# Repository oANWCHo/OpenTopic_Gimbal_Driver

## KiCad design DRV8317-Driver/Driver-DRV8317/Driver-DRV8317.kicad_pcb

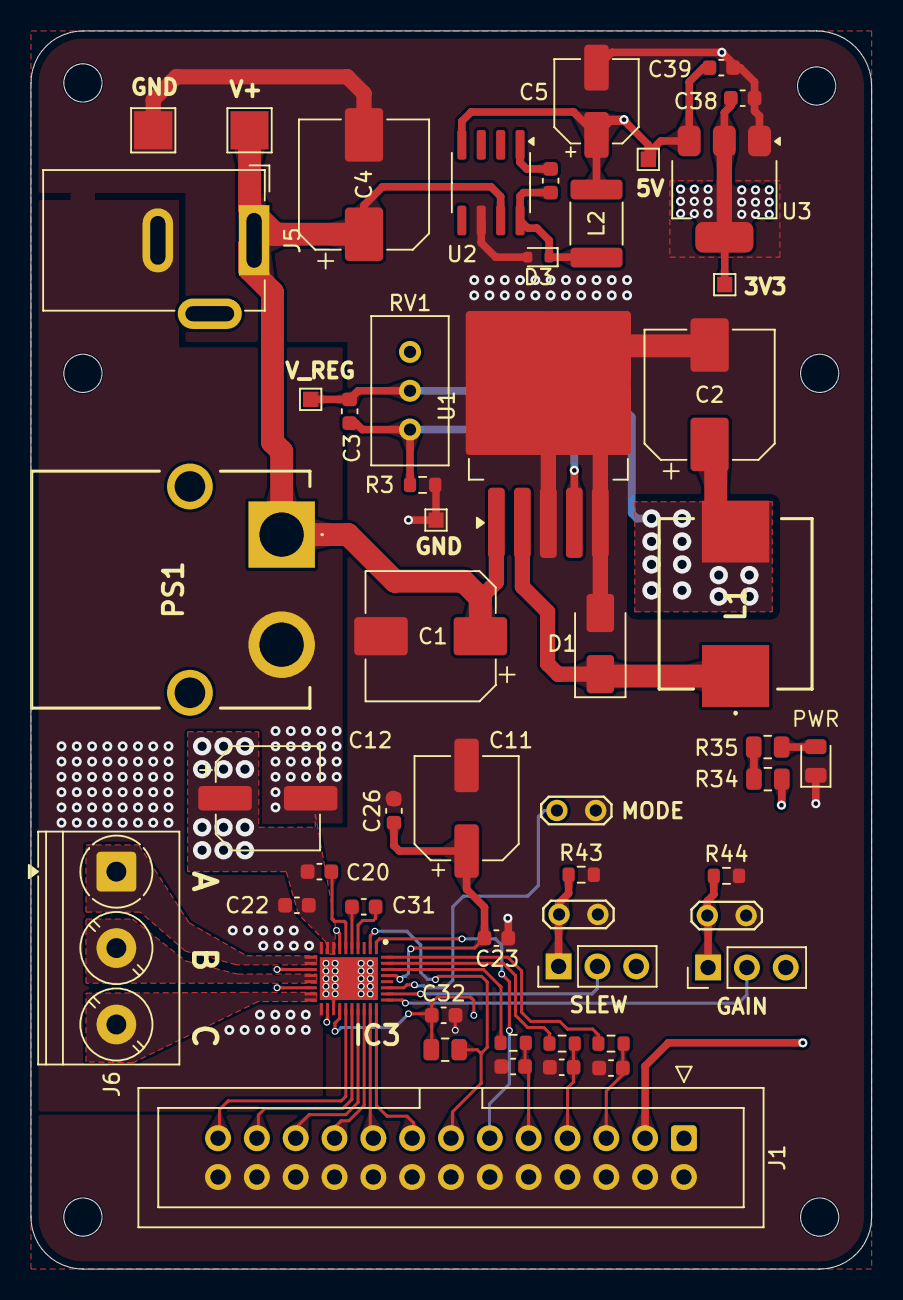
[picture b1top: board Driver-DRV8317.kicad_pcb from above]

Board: 4 copper layers, 55.0 x 81.0 mm, 59 parts (0 on the bottom side), 36 nets.

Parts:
C1: 330uF 35V; CP_Elec_8x10
C2, C4: 330uF 25V; CP_Elec_8x10
C3: 1.5nF; C_0603_1608Metric
C5: 100uF 10V; CP_Elec_5x5.3
C11, C12: 22uF 25V; CP_Elec_6.3x5.4
C20, C22, C23, C26, C31, C39: 0.1uF; C_0603_1608Metric
C28: 10nF; C_0603_1608Metric
C32: 2.2uF; C_0603_1608Metric
C33, C34, C35: 22pF; C_0603_1608Metric
C38: 10uF; C_0603_1608Metric
D1: 60V 3A; D_SMA
D3: 20V 500mA; D_SOD-523
D5: Red LED; LED_0805_2012Metric
H1, H2, H3, H4, H5, H6: MountingHole; MountingHole_2.5mm
IC3: DRV8317HREER; QFN40P400X500X80-37N-D
J1: Conn_02x13_Odd_Even; IDC-Header_2x13_P2.54mm_Vertical
J5: Jack-DC; BarrelJack_GCT_DCJ200-10-A_Horizontal
J6: Screw_Terminal_01x03; TerminalBlock_Phoenix_PT-1,5-3-5.0-H_1x03_P5.00mm_Horizontal
JP1: 0.25V/A; TestPoint_2Pads_Pitch2.54mm_Drill0.8mm
JP2: Gain Selector; PinHeader_1x03_P2.54mm_Vertical
JP3: Mode Selector; TestPoint_2Pads_Pitch2.54mm_Drill0.8mm
JP4: Slew Selector; PinHeader_1x03_P2.54mm_Vertical
JP5: 25V/us; TestPoint_2Pads_Pitch2.54mm_Drill0.8mm
L1: 47uH 3.1A; LMLP1011M470DTAS
L2: 47uH 3.1A; L_1812_4532Metric_Pad1.30x3.40mm_HandSolder
PS1: XT60PW-M; XT60PWM
R3: 1K; R_0603_1608Metric
R4, R5, R6: 330; R_0603_1608Metric
R34, R35: 3.6; R_0805_2012Metric
R42: 5k; R_0805_2012Metric
R43, R44: 47K; R_0603_1608Metric
RV1: R_Potentiometer_Trim; Potentiometer_Bourns_3296W_Vertical
TP1, TP2, TP3, TP7: TestPoint; TestPoint_Pad_1.0x1.0mm
TP8: V+; TestPoint_Pad_2.5x2.5mm
TP9: V-; TestPoint_Pad_2.5x2.5mm
U1: LM2596S-ADJ; TO-263-5_TabPin3
U2: LM2674M-5.0; SOIC-8_3.9x4.9mm_P1.27mm
U3: LD1117S33TR; SOT-223-3_TabPin2

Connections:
+5V: C5.1, C39.2, J1.3, L2.2, TP3.1, U2.4 (FB), U3.3 (VI)
/DRV8317/NFAULT: IC3.2 (NFAULT), J1.13, R42.1
/DRV8317/NSLEEP: IC3.1 (NSLEEP), J1.11
/DRV8317/TIM1_CH1: IC3.23 (INHA), J1.25
/DRV8317/TIM1_CH1N: IC3.24 (INLA), J1.23
/DRV8317/TIM1_CH2: IC3.25 (INHB), J1.21
/DRV8317/TIM1_CH2N: IC3.26 (INLB), J1.19
/DRV8317/TIM1_CH3: IC3.27 (INHC), J1.17
/DRV8317/TIM1_CH3N: IC3.28 (INLC), J1.15
/DRV8317/Vcurrfdbk_A: IC3.36 (SOA), R4.1
/DRV8317/Vcurrfdbk_B: IC3.35 (SOB), R5.1
/DRV8317/Vcurrfdbk_C: IC3.34 (SOC), R6.1
AVDD: C11.1, C23.1, C26.1, C32.1, C38.2, IC3.7 (VIN_AVDD), IC3.22 (AVDD), IC3.33 (CSAREF), J1.1, JP2.3 (B), JP4.3 (B), R34.1, R42.2, TP7.1, U3.2 (VO)
CP: C20.2, IC3.6 (CP)
CPH: C31.2, IC3.5 (CPH)
CPL: C31.1, IC3.4 (CPL)
GAIN: IC3.29 (GAIN), JP2.2 (C)
GND: C1.2, C2.2, C4.2, C5.2, C11.2, C12.2, C22.2, C23.2, C26.2, C32.2, C33.1, C34.1, C35.1, C38.1, C39.1, D1.2 (A), D3.2 (A), D5.1 (K), IC3.10 (PGND_1), IC3.13 (PGND_2), IC3.16 (PGND_3), IC3.19 (PGND_4), IC3.21 (AGND), IC3.37 (GND), J1.2, J1.4, J1.6, J1.8, J1.10, J1.12, J1.14, J1.16, J1.18, J1.20, J1.22, J1.24, J1.26, J5.2, JP1.2 (B), JP3.2 (B), JP5.2 (B), PS1.2 (-), R3.1, R43.2, R44.2, TP2.1, TP9.1, U1.3 (GND), U1.5 (~ON/OFF), U2.6 (GND), U3.1 (GND)
MODE: IC3.31 (MODE), JP3.1 (A)
unnamed: D1.1 (K), L1.1, U1.2 (OUT)
unnamed: C28.2, D3.1 (K), L2.1, U2.8 (VSW)
unnamed: D5.2 (A), R35.2
unnamed: IC3.11 (OUTA_1), IC3.12 (OUTA_2), J6.1
unnamed: IC3.14 (OUTB_1), IC3.15 (OUTB_2), J6.2
unnamed: IC3.17 (OUTC_1), IC3.18 (OUTC_2), J6.3
unnamed: C33.2, J1.5, R4.2
unnamed: C34.2, J1.7, R5.2
unnamed: C35.2, J1.9, R6.2
unnamed: JP1.1 (A), JP2.1 (A), R44.1
unnamed: JP4.1 (A), JP5.1 (A), R43.1
unnamed: R34.2, R35.1
unnamed: C3.1, R3.2, RV1.1, U1.4 (FB)
unnamed: C28.1, U2.1 (CB)
SLEW: IC3.30 (SLEW), JP4.2 (C)
V+: C1.1, C4.1, J5.1, PS1.1 (+), TP8.1, U1.1 (VIN), U2.7 (VIN)
VM: C2.1, C3.2, C12.1, C20.1, C22.1, IC3.8 (VM_1), IC3.9 (VM_2), IC3.20 (VM_3), L1.2, RV1.2, TP1.1

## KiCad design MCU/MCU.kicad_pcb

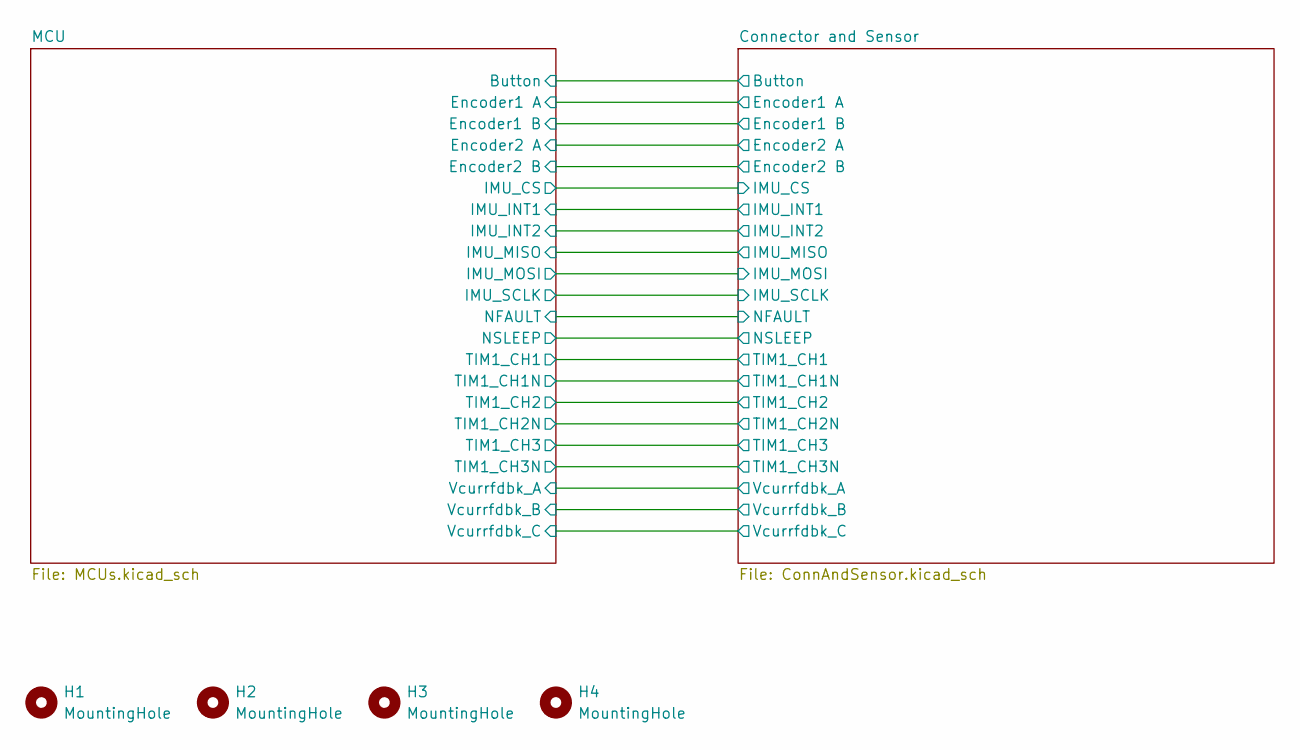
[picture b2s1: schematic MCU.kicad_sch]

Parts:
H1, H2, H3, H4: MountingHole; MountingHole_2.5mm

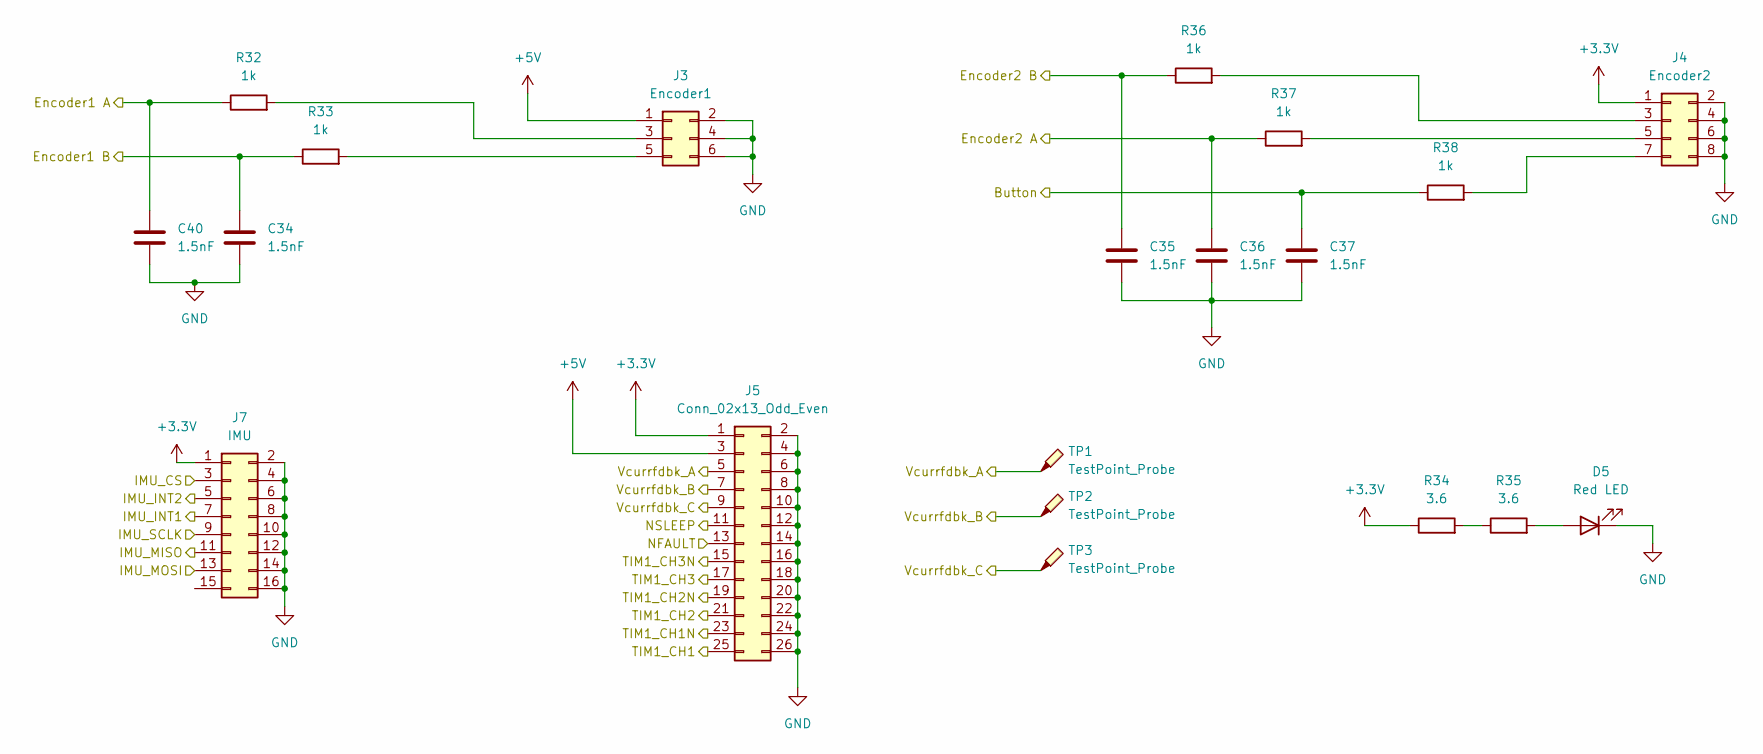
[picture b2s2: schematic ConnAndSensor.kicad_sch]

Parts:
C34, C35, C36, C37, C40: 1.5nF; C_0603_1608Metric
D5: Red LED; LED_0805_2012Metric
J3: Encoder1; IDC-Header_2x03_P2.54mm_Vertical
J4: Encoder2; IDC-Header_2x04_P2.54mm_Vertical
J5: Conn_02x13_Odd_Even; IDC-Header_2x13_P2.54mm_Vertical
J7: IMU; IDC-Header_2x08_P2.54mm_Vertical
R32, R33, R36, R37, R38: 1k; R_0603_1608Metric
R34, R35: 3.6; R_0805_2012Metric
TP1, TP2, TP3: TestPoint_Probe; TestPoint_Loop_D1.80mm_Drill1.0mm_Beaded

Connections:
+5V: J3.1, J5.3
/Connector and Sensor/Button: C37.2, R38.1; also elsewhere on the board
/Connector and Sensor/Encoder1 A: C40.2, R32.1; also elsewhere on the board
/Connector and Sensor/Encoder1 B: C34.2, R33.1; also elsewhere on the board
/Connector and Sensor/Encoder2 A: C36.2, R37.1; also elsewhere on the board
/Connector and Sensor/Encoder2 B: C35.2, R36.1; also elsewhere on the board
/Connector and Sensor/IMU_CS: J7.3; also elsewhere on the board
/Connector and Sensor/IMU_INT1: J7.7; also elsewhere on the board
/Connector and Sensor/IMU_INT2: J7.5; also elsewhere on the board
/Connector and Sensor/IMU_MISO: J7.11; also elsewhere on the board
/Connector and Sensor/IMU_MOSI: J7.13; also elsewhere on the board
/Connector and Sensor/IMU_SCLK: J7.9; also elsewhere on the board
/Connector and Sensor/NFAULT: J5.13; also elsewhere on the board
/Connector and Sensor/NSLEEP: J5.11; also elsewhere on the board
/Connector and Sensor/TIM1_CH1: J5.25; also elsewhere on the board
/Connector and Sensor/TIM1_CH1N: J5.23; also elsewhere on the board
/Connector and Sensor/TIM1_CH2: J5.21; also elsewhere on the board
/Connector and Sensor/TIM1_CH2N: J5.19; also elsewhere on the board
/Connector and Sensor/TIM1_CH3: J5.17; also elsewhere on the board
/Connector and Sensor/TIM1_CH3N: J5.15; also elsewhere on the board
/Connector and Sensor/Vcurrfdbk_A: J5.5, TP1.1; also elsewhere on the board
/Connector and Sensor/Vcurrfdbk_B: J5.7, TP2.1; also elsewhere on the board
/Connector and Sensor/Vcurrfdbk_C: J5.9, TP3.1; also elsewhere on the board
GND: C34.1, C35.1, C36.1, C37.1, C40.1, D5.1 (K), J3.2, J3.4, J3.6, J4.2, J4.4, J4.6, J4.8, J5.2, J5.4, J5.6, J5.8, J5.10, J5.12, J5.14, J5.16, J5.18, J5.20, J5.22, J5.24, J5.26, J7.2, J7.4, J7.6, J7.8, J7.10, J7.12, J7.14, J7.16; also elsewhere on the board
unnamed: D5.2 (A), R35.2
unnamed: J3.3, R32.2
unnamed: J3.5, R33.2
unnamed: J4.3, R36.2
unnamed: J4.5, R37.2
unnamed: J4.7, R38.2
unnamed: R34.2, R35.1
VDD: J4.1, J5.1, J7.1, R34.1; also elsewhere on the board

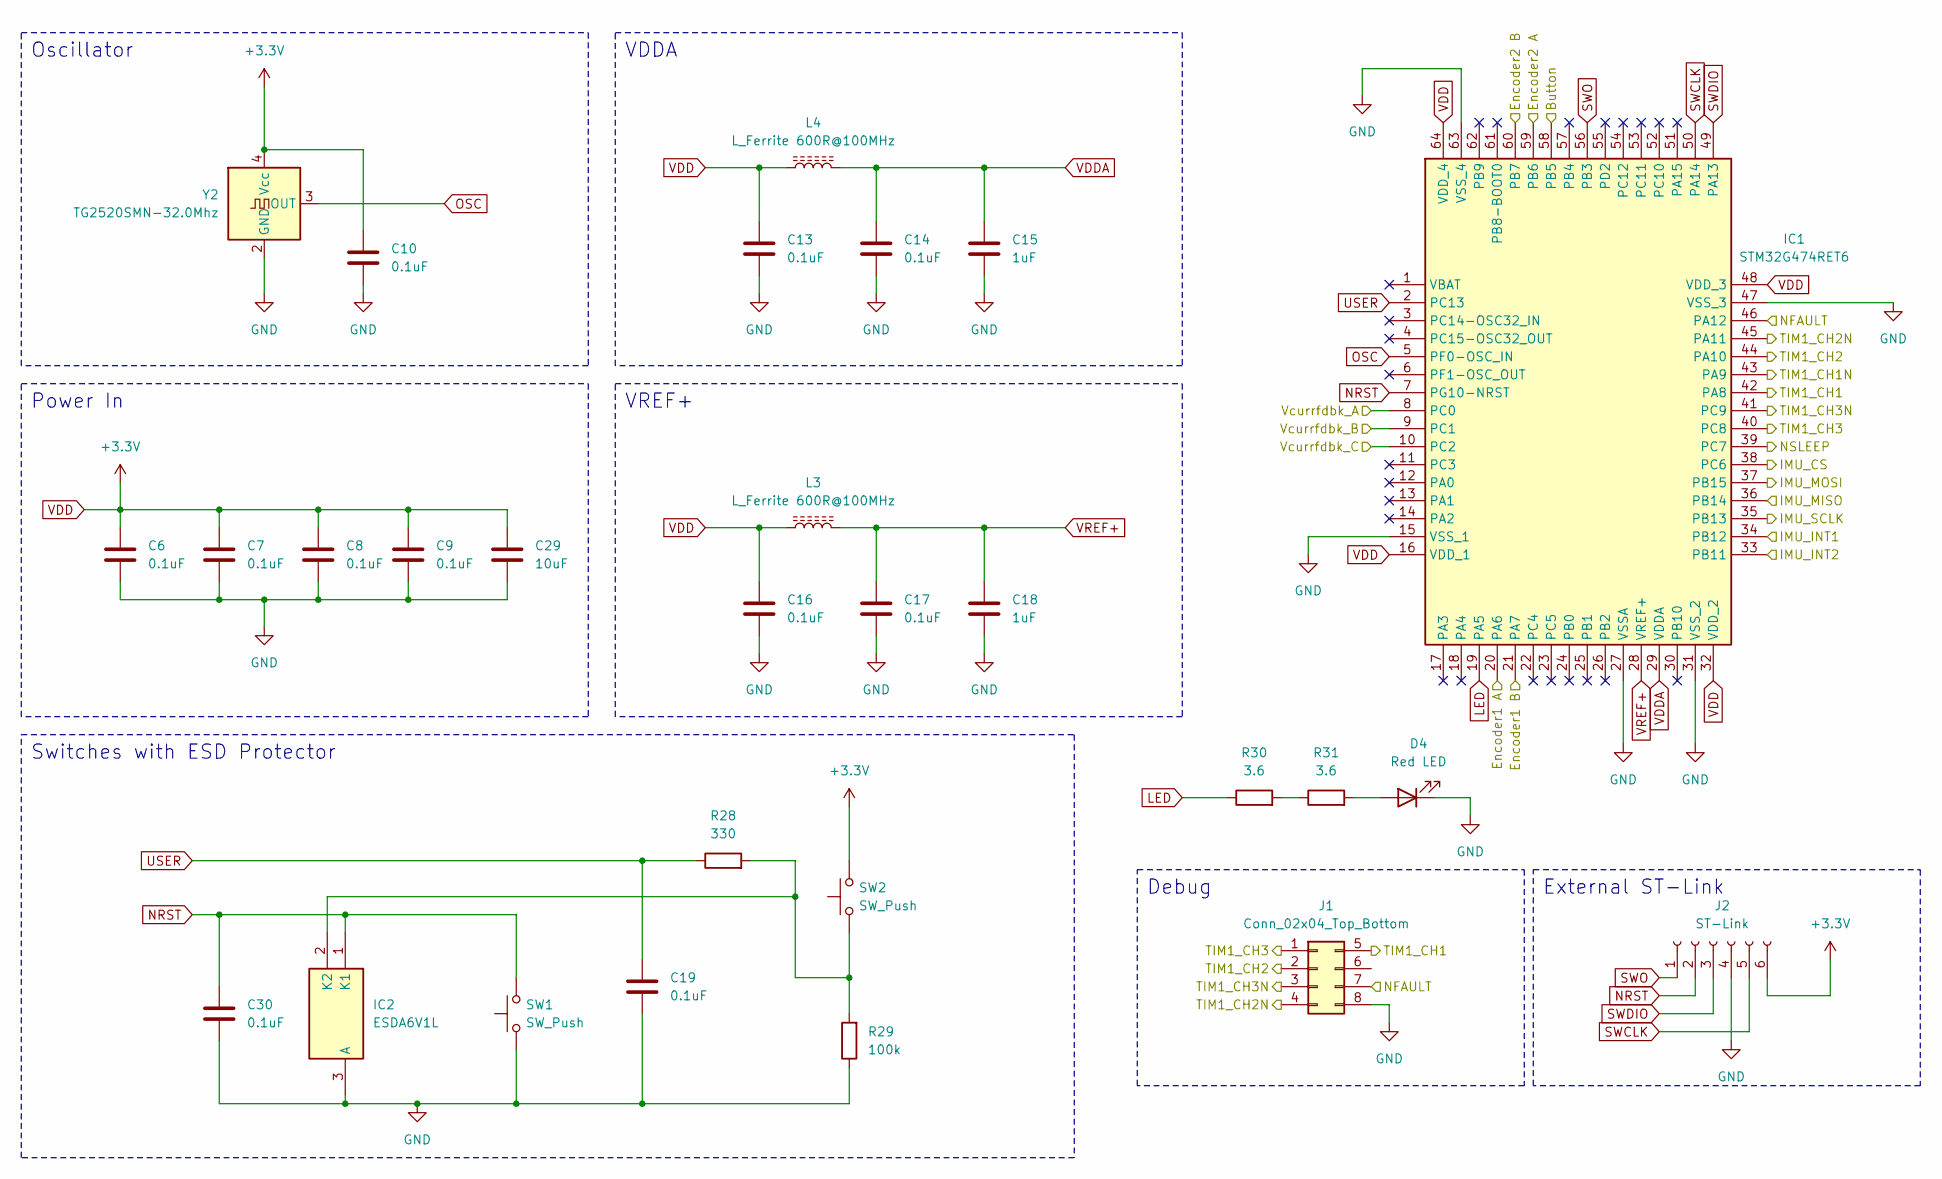
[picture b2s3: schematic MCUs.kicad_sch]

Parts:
C6, C7, C8, C9, C10, C13, C14, C16, C17, C19, C30: 0.1uF; C_0603_1608Metric
C15, C18: 1uF; C_0603_1608Metric
C29: 10uF; C_0603_1608Metric
D4: Red LED; LED_0805_2012Metric
IC1: STM32G474RET6; QFP50P1200X1200X160-64N; Mouser Part Number 511-STM32G474RET6
IC2: ESDA6V1L; SOT105P242X150-3N; Mouser Part Number 511-ESDA6V1L
J1: Conn_02x04_Top_Bottom; PinHeader_2x04_P2.54mm_Vertical
J2: ST-Link; JST_EH_B6B-EH-A_1x06_P2.50mm_Vertical
L3, L4: L_Ferrite 600R@100MHz; R_0603_1608Metric
R28: 330; R_0603_1608Metric
R29: 100k; R_0603_1608Metric
R30, R31: 3.6; R_0805_2012Metric
SW1, SW2: SW_Push; SW_Tactile_SPST_NO_Straight_CK_PTS636Sx25SMTRLFS
Y2: TG2520SMN-32.0Mhz; Oscillator_SMD_SeikoEpson_TG2520SMN-xxx-xxxxxx-4Pin_2.5x2.0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

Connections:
/Connector and Sensor/Button: IC1.58 (PB5); also elsewhere on the board
/Connector and Sensor/Encoder1 A: IC1.20 (PA6); also elsewhere on the board
/Connector and Sensor/Encoder1 B: IC1.21 (PA7); also elsewhere on the board
/Connector and Sensor/Encoder2 A: IC1.59 (PB6); also elsewhere on the board
/Connector and Sensor/Encoder2 B: IC1.60 (PB7); also elsewhere on the board
/Connector and Sensor/IMU_CS: IC1.38 (PC6); also elsewhere on the board
/Connector and Sensor/IMU_INT1: IC1.34 (PB12); also elsewhere on the board
/Connector and Sensor/IMU_INT2: IC1.33 (PB11); also elsewhere on the board
/Connector and Sensor/IMU_MISO: IC1.36 (PB14); also elsewhere on the board
/Connector and Sensor/IMU_MOSI: IC1.37 (PB15); also elsewhere on the board
/Connector and Sensor/IMU_SCLK: IC1.35 (PB13); also elsewhere on the board
/Connector and Sensor/NFAULT: IC1.46 (PA12), J1.7; also elsewhere on the board
/Connector and Sensor/NSLEEP: IC1.39 (PC7); also elsewhere on the board
/Connector and Sensor/TIM1_CH1: IC1.42 (PA8), J1.5; also elsewhere on the board
/Connector and Sensor/TIM1_CH1N: IC1.43 (PA9); also elsewhere on the board
/Connector and Sensor/TIM1_CH2: IC1.44 (PA10), J1.2; also elsewhere on the board
/Connector and Sensor/TIM1_CH2N: IC1.45 (PA11), J1.4; also elsewhere on the board
/Connector and Sensor/TIM1_CH3: IC1.40 (PC8), J1.1; also elsewhere on the board
/Connector and Sensor/TIM1_CH3N: IC1.41 (PC9), J1.3; also elsewhere on the board
/Connector and Sensor/Vcurrfdbk_A: IC1.8 (PC0); also elsewhere on the board
/Connector and Sensor/Vcurrfdbk_B: IC1.9 (PC1); also elsewhere on the board
/Connector and Sensor/Vcurrfdbk_C: IC1.10 (PC2); also elsewhere on the board
GND: C6.1, C7.1, C8.1, C9.1, C10.2, C13.2, C14.2, C15.2, C16.2, C17.2, C18.2, C19.2, C29.1, C30.2, D4.1 (K), IC1.15 (VSS_1), IC1.27 (VSSA), IC1.31 (VSS_2), IC1.47 (VSS_3), IC1.63 (VSS_4), IC2.3 (A), J1.8, J2.4, R29.1, SW1.1, Y2.2 (GND); also elsewhere on the board
LED: IC1.19 (PA5), R30.1
NRST: C30.1, IC1.7 (PG10-NRST), IC2.1 (K1), J2.2, SW1.2
unnamed: D4.2 (A), R31.2
unnamed: IC2.2 (K2), R28.2, R29.2, SW2.1
unnamed: R30.2, R31.1
OSC: IC1.5 (PF0-OSC_IN), Y2.3 (OUT)
SWCLK: IC1.50 (PA14), J2.5
SWDIO: IC1.49 (PA13), J2.3
SWO: IC1.56 (PB3), J2.1
USER: C19.1, IC1.2 (PC13), R28.1
VDD: C6.2, C7.2, C8.2, C9.2, C10.1, C13.1, C16.1, C29.2, IC1.16 (VDD_1), IC1.32 (VDD_2), IC1.48 (VDD_3), IC1.64 (VDD_4), J2.6, L3.1, L4.1, SW2.2, Y2.4 (Vcc); also elsewhere on the board
VDDA: C14.1, C15.1, IC1.29 (VDDA), L4.2
VREF+: C17.1, C18.1, IC1.28 (VREF+), L3.2

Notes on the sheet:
External ST-Link
VREF+
Oscillator
Power In
Switches with ESD Protector
Debug
VDDA

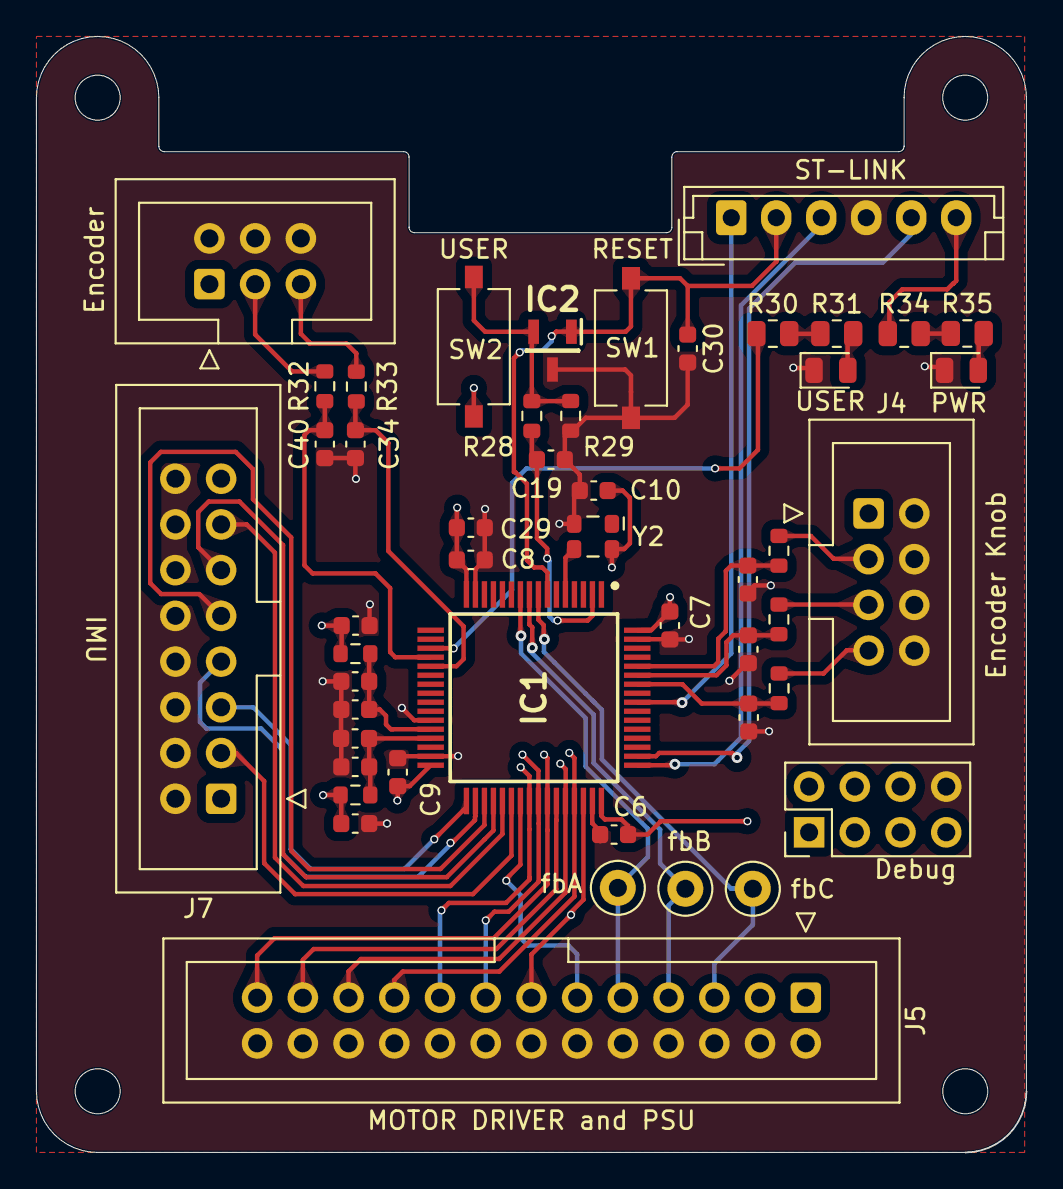
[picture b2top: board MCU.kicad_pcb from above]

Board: 4 copper layers, 55.0 x 62.0 mm, 52 parts (0 on the bottom side), 44 nets.

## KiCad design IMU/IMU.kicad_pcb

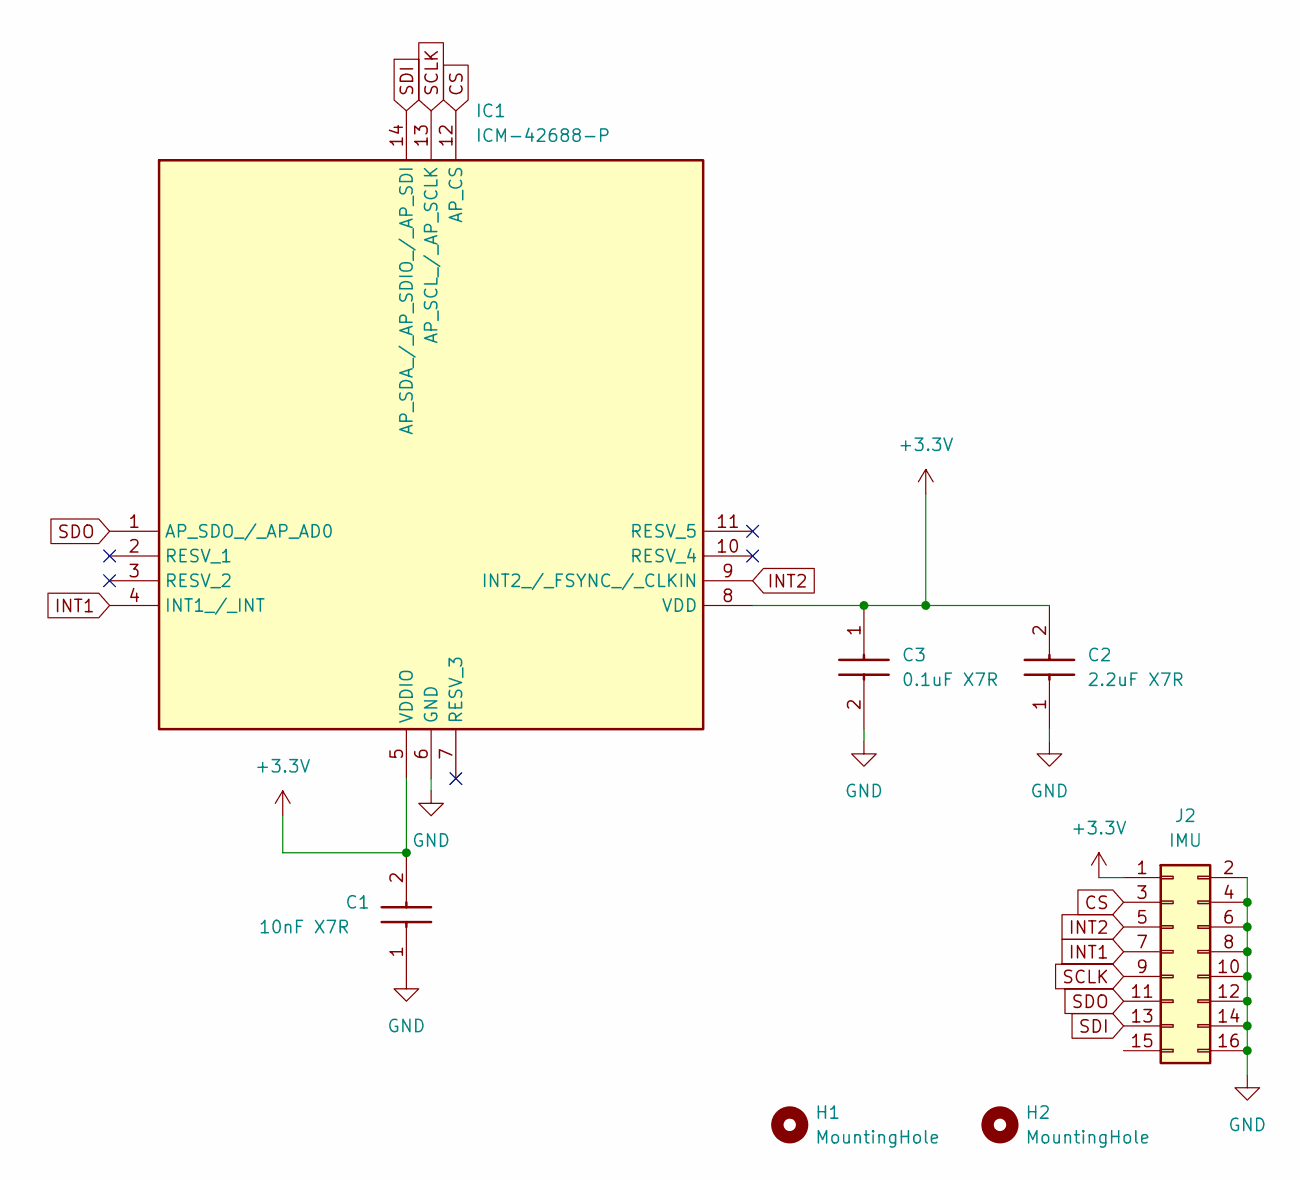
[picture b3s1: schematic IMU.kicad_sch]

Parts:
C1: 10nF X7R; CAPC2012X94N; Mouser Part Number 581-KAF21BR72A103JT
C2: 2.2uF X7R; CAPC2012X152N; Mouser Part Number 581-08056C225KAT2A
C3: 0.1uF X7R; CAPC2012X94N; Mouser Part Number 581-KAM21BR71H104JT
H1, H2: MountingHole; MountingHole_3.2mm_M3
IC1: ICM-42688-P; IIM42352; Mouser Part Number 410-ICM-42688-P
J2: IMU; IDC-Header_2x08_P2.54mm_Vertical

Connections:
+3.3V: C1.2, C2.2, C3.1, IC1.5 (VDDIO), IC1.8 (VDD), J2.1
CS: IC1.12 (AP_CS), J2.3
GND: C1.1, C2.1, C3.2, IC1.6 (GND), J2.2, J2.4, J2.6, J2.8, J2.10, J2.12, J2.14, J2.16
INT1: IC1.4 (INT1_/_INT), J2.7
INT2: IC1.9 (INT2_/_FSYNC_/_CLKIN), J2.5
SCLK: IC1.13 (AP_SCL_/_AP_SCLK), J2.9
SDI: IC1.14 (AP_SDA_/_AP_SDIO_/_AP_SDI), J2.13
SDO: IC1.1 (AP_SDO_/_AP_AD0), J2.11

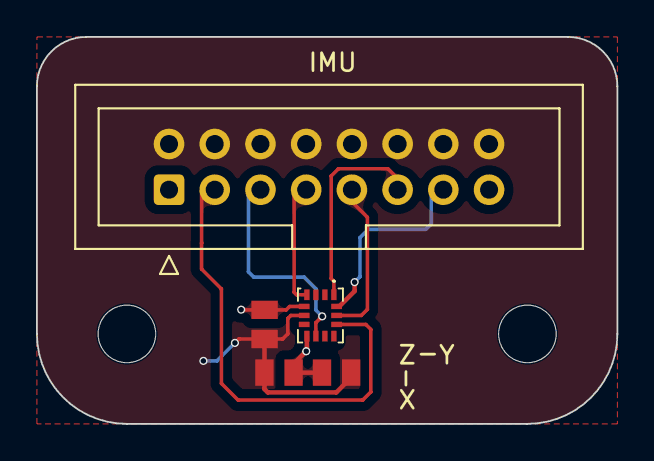
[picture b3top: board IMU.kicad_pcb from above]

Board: 2 copper layers, 32.2 x 21.5 mm, 7 parts (0 on the bottom side), 8 nets.

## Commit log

2025-03-01 Init
2025-03-02 Clear all Error in DRC
2025-03-02 Add user Label
2025-03-02 Update a Connector and Trimpot
2025-03-05 Big Change
    Seperate a boards
2025-03-05 kncoadsnofijasndvoi
2025-03-07 fix all via to 0.45/0.3 mm
